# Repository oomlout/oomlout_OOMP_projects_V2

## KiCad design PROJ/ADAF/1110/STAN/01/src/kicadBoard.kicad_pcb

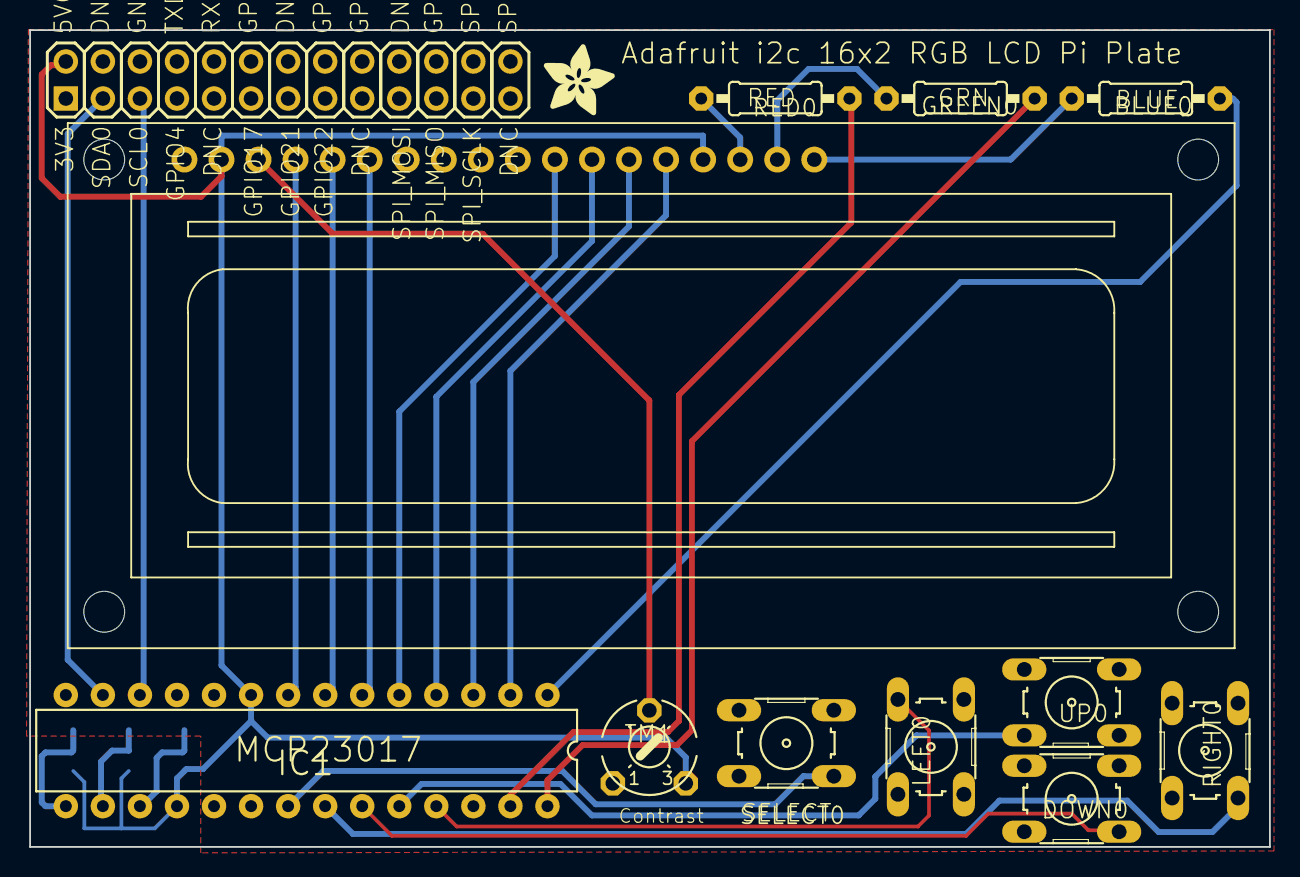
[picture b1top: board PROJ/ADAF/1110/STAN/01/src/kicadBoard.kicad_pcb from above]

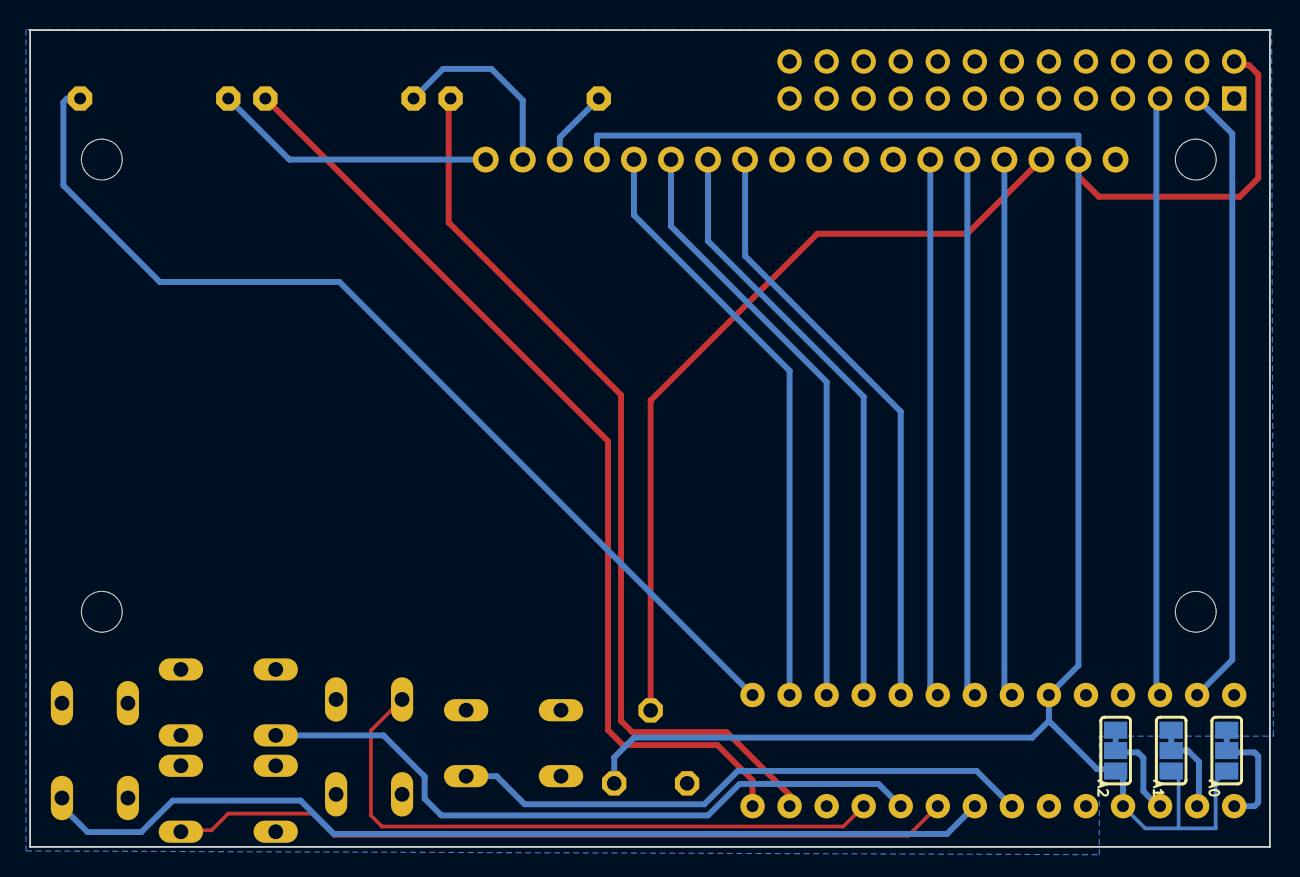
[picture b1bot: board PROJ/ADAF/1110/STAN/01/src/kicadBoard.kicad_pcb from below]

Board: 16 copper layers, 85.0 x 56.0 mm, 16 parts (3 on the bottom side), 23 nets.

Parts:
A0, A1, A2: SOLDERJUMPER_2WAY_OPEN_NOPASTE
BLUE0: 220; 0207_10
DOWN0: B3F-10XX
GREEN0: 330; 0207_10
IC1: MCP23017SP2; DIL28-3-ROUND
LEFT0: B3F-10XX
RED0: 220; 0207_10
RIGHT0: B3F-10XX
SELECT0: B3F-10XX
TM1: 10K; 6MM
U$1: HD44780LCD_RGBLONGPINS; LCD1602-RGB
U$2: ADAFRUIT_5MM
U$4: RASPBERRYPI_BB; RASBERRYPI_SHIELD
UP0: B3F-10XX

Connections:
+5V: A0.1, A1.1, A2.1, IC1.9, IC1.18, TM1.E, U$1.2, U$1.15, U$4.2
GND: A0.2, A0.3, A1.2, A1.3, A2.2, A2.3, DOWN0.2, IC1.10, IC1.15, IC1.16, IC1.17, LEFT0.2, RIGHT0.2, SELECT0.2, TM1.A, U$1.1, U$4.6, UP0.2
GPA0: IC1.21, SELECT0.4
GPA1: IC1.22, RIGHT0.3
GPA2: DOWN0.4, IC1.23
GPA3: IC1.24, UP0.3
GPA4: IC1.25, LEFT0.3
GPA6: IC1.27, RED0.2
GPA7: GREEN0.1, IC1.28
GPB0: BLUE0.2, IC1.1
GPB1: IC1.2, U$1.14
GPB2: IC1.3, U$1.13
GPB3: IC1.4, U$1.12
GPB4: IC1.5, U$1.11
GPB5: IC1.6, U$1.6
GPB6: IC1.7, U$1.5
GPB7: IC1.8, U$1.4
unnamed: BLUE0.1, U$1.18
unnamed: GREEN0.2, U$1.17
unnamed: RED0.1, U$1.16
unnamed: TM1.S, U$1.3
SCL: IC1.12, U$4.5
SDA: IC1.13, U$4.3

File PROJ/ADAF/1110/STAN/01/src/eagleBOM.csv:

"Part";"Value";"Device";"Package";"Description";"";
"A0";"";"SOLDERJUMPER_2WAY";"SOLDERJUMPER_2WAY_OPEN_NOPASTE";"2-Way Solder Jumper";"";
"A1";"";"SOLDERJUMPER_2WAY";"SOLDERJUMPER_2WAY_OPEN_NOPASTE";"2-Way Solder Jumper";"";
"A2";"";"SOLDERJUMPER_2WAY";"SOLDERJUMPER_2WAY_OPEN_NOPASTE";"2-Way Solder Jumper";"";
"BLUE";"220";"R-US_0207/10";"0207/10";"RESISTOR, American symbol";"";
"DOWN";"";"10-XX";"B3F-10XX";"OMRON SWITCH";"";
"GREEN";"330";"R-US_0207/10";"0207/10";"RESISTOR, American symbol";"";
"IC1";"MCP23017SP2";"MCP23017SP2";"DIL28-3-ROUND";"http://ww1.microchip.com/downloads/en/DeviceDoc/21952a.pdf";"";
"LEFT";"";"10-XX";"B3F-10XX";"OMRON SWITCH";"";
"RED";"220";"R-US_0207/10";"0207/10";"RESISTOR, American symbol";"";
"RIGHT";"";"10-XX";"B3F-10XX";"OMRON SWITCH";"";
"SELECT";"";"10-XX";"B3F-10XX";"OMRON SWITCH";"";
"TM1";"10K";"TRIM";"6MM";"";"";
"U$1";"HD44780LCD_RGBLONGPINS";"HD44780LCD_RGBLONGPINS";"LCD1602-RGB";"";"";
"U$4";"RASPBERRYPI_BB";"RASPBERRYPI_BB";"RASBERRYPI_SHIELD";"";"";
"UP";"";"10-XX";"B3F-10XX";"OMRON SWITCH";"";

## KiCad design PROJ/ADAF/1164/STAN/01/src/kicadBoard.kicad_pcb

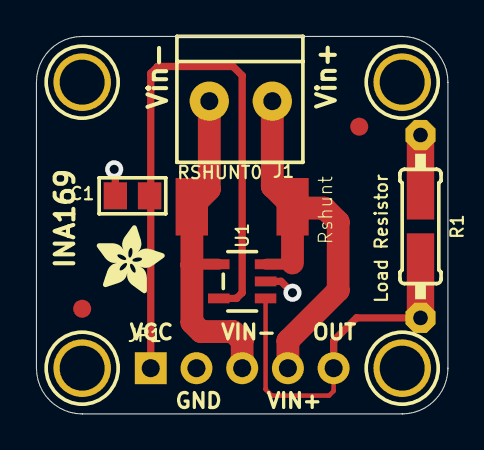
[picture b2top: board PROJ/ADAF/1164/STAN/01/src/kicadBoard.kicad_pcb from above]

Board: 2 copper layers, 22.9 x 21.0 mm, 13 parts (0 on the bottom side), 5 nets.

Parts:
C1: 0.1µF; 0805
FID1, FID2: FIDUCIAL""; FIDUCIAL_1MM
J1: TERMBLOCK_1X2-3.5MM
JP1: 1X05_ROUND_70
R1: 10K; 0805-THM
RSHUNT0: 0.1/1% (PT2512FK-070R1L); 2512
U1: INA169; SOT23-5
U$7, U$8, U$9, U$10: MOUNTINGHOLE2.5; MOUNTINGHOLE_2.5_PLATED
U$11: ADAFRUIT_3.5MM

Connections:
GND: C1.2, JP1.2, R1.2, U1.2
OUT: JP1.5, R1.1, U1.1
VCC: C1.1, JP1.1, U1.5
VIN+: J1.2, JP1.4, RSHUNT0.2, U1.3
VIN-: J1.1, JP1.3, RSHUNT0.1, U1.4

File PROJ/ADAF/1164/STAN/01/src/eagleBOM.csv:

"Part";"Value";"Device";"Package";"Description";"BOM";
"C1";"0.1µF";"CAP_CERAMIC0805";"0805";"Ceramic Capacitors";"";
"FID1";"FIDUCIAL""";"FIDUCIAL""";"FIDUCIAL_1MM";"Fiducial Alignment Points";"EXCLUDE";
"FID2";"FIDUCIAL""";"FIDUCIAL""";"FIDUCIAL_1MM";"Fiducial Alignment Points";"EXCLUDE";
"J1";"";"TERMBLOCK_1X2";"TERMBLOCK_1X2-3.5MM";"3.5mm Terminal block";"";
"JP1";"";"HEADER-1X570MIL";"1X05_ROUND_70";"PIN HEADER";"";
"R1";"10K";"RESISTOR_DUAL";"0805-THM";"Flip Flop resistor";"";
"RSHUNT";"0.1/1% (PT2512FK-070R1L)";"RESISTOR2512";"2512";"Resistors";"";
"U$7";"MOUNTINGHOLE2.5";"MOUNTINGHOLE2.5";"MOUNTINGHOLE_2.5_PLATED";"Mounting Hole";"";
"U$8";"MOUNTINGHOLE2.5";"MOUNTINGHOLE2.5";"MOUNTINGHOLE_2.5_PLATED";"Mounting Hole";"";
"U$9";"MOUNTINGHOLE2.5";"MOUNTINGHOLE2.5";"MOUNTINGHOLE_2.5_PLATED";"Mounting Hole";"";
"U$10";"MOUNTINGHOLE2.5";"MOUNTINGHOLE2.5";"MOUNTINGHOLE_2.5_PLATED";"Mounting Hole";"";
"U1";"INA169";"INA169";"SOT23-5";"INA169 - High-Side Measurement Current Shunt Monitor";"";

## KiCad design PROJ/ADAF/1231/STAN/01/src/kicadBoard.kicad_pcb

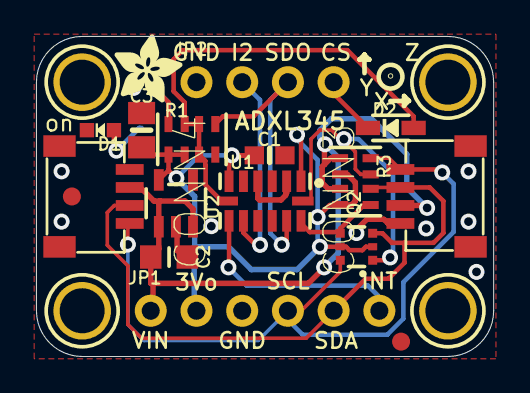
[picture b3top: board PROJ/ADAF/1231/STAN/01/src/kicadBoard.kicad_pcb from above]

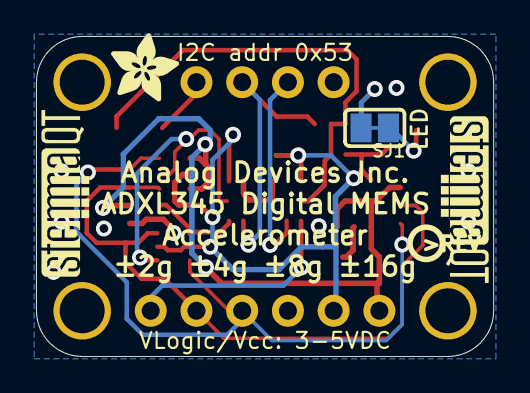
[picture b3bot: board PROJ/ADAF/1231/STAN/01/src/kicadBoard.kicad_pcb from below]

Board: 2 copper layers, 25.4 x 17.8 mm, 26 parts (5 on the bottom side), 14 nets.

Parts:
C1: 0.1uF; 0603-NO
C2: 10uF; _0805MP
C3: 10uF; 0805-NO
CONN3, CONN4: STEMMA_I2C_QT; JST_SH4
D1: GREEN; CHIPLED_0603_NOOUTLINE
D2: 1N4148; SOD-323
FID3, FID4: FIDUCIAL_1MM
JP1: 1X06_ROUND_70
JP2: 1X04_ROUND
Q2: BSS138; SOT363
R1, R3: 10K; RESPACK_4X0603
SJ1: SOLDERJUMPER_CLOSEDWIRE
U1: ADXL343; LGA14
U2: AP2112K-3.3; SOT23-5
U$1, U$17, U$19, U$21: MOUNTINGHOLE2.5; MOUNTINGHOLE_2.5_PLATED
U$4, U$11: ADAFRUIT_3.5MM
U$25: PCBFEAT-REV-040
U$30, U$31: STEMMAQT

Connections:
3.3V: C1.1, C3.1, JP1.2, Q2.2, Q2.5, R1.1, R1.2, R3.2, R3.4, U1.1, U1.6, U2.5
CS: D2.C, JP2.4
CS_3V: D2.A, R1.3, R1.6, R1.7, U1.7
GND: C1.2, C2.2, C3.2, CONN3.1, CONN3.MT1, CONN3.MT2, CONN4.1, CONN4.MT1, CONN4.MT2, D1.C, JP1.3, JP2.1, R1.4, U1.2, U1.4, U1.5, U2.2
INT1: JP1.6, U1.8
INT2: JP2.2, U1.9
unnamed: R1.8, SJ1.2
unnamed: D1.A, SJ1.1
SCL: CONN3.4, CONN4.4, JP1.4, Q2.6, R3.8
SCL_3V: Q2.1, R3.7, U1.14
SDA/SDIO: CONN3.3, CONN4.3, JP1.5, Q2.3, R3.6
SDA/SDIO_3V: Q2.4, R3.5, U1.13
SDO: JP2.3, R1.5, U1.12
VCC: C2.1, CONN3.2, CONN4.2, JP1.1, R3.1, R3.3, U2.1, U2.3

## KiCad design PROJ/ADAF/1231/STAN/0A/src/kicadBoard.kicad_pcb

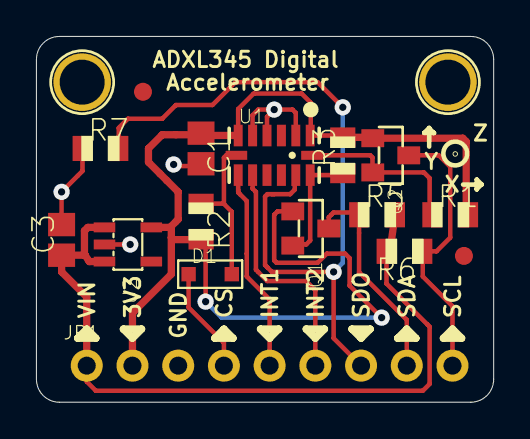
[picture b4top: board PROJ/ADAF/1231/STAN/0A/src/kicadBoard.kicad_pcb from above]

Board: 2 copper layers, 25.4 x 20.3 mm, 19 parts (1 on the bottom side), 12 nets.

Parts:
C1: 0.1uF; C0805
C3: 10µF; C0805
D1: 1N4148; SOD-323
JP1: 1X09_ROUND_70
Q1, Q2: BSS138; SOT23-WIDE
R1, R2, R3, R5, R6, R7: 10K; R0805
U1: LGA14
U2: SOT23-5
U$1, U$3: FIDUCIAL; FIDUCIAL_1MM
U$4, U$6: MOUNTINGHOLE2.5; MOUNTINGHOLE_2.5_PLATED
U$7: ADAFRUIT_TEXT_20MM

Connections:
3.3V: C1.1, JP1.2, Q1.1, Q2.1, R1.2, R2.2, R3.2, U1.1, U1.6, U2.5
CS: D1.A, R2.1, U1.7
CS_5V: D1.C, JP1.4
GND: C1.2, C3.2, JP1.3, R7.1, U1.2, U1.4, U1.5, U2.2
INT1: JP1.5, U1.8
INT2: JP1.6, U1.9
SCL: Q2.2, R1.1, U1.14
SCL_5V: JP1.9, Q2.3, R6.1
SDA/SDIO: Q1.2, R3.1, U1.13
SDA/SDIO_5V: JP1.8, Q1.3, R5.1
SDO/ADDR: JP1.7, R7.2, U1.12
VIN: C3.1, JP1.1, R5.2, R6.2, U2.1, U2.3
